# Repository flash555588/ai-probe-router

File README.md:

# ai-probe-router

AI-assisted KiCad probe/test interface designer. Automatically generates testpoints, maps probe pins to development board connectors, and validates placement against electrical, mechanical, and manufacturing constraints.

## Features

- **KiCad S-expression parser** — reads `.kicad_sch` and `.kicad_pcb` files, supports `gr_rect`, `gr_line`, `gr_circle` board outlines
- **Net classifier** — rule-based classification into power, ground, debug, communication, analog, high-speed, clock, reset, GPIO
- **Constraint-aware placement** — generates candidate positions scored by routing cost, board edge clearance, component collision avoidance, and probe spacing
- **Pin mapper** — maps target nets to development board pins using capability matching, current ratings, and user preferences
- **Schematic + PCB generation** — inserts testpoint symbols/footprints, connector symbols/footprints, protection circuits, fiducials, tooling holes, and keepout zones into KiCad files
- **Protection circuit generation** — series resistors for debug/reset signals (33/100 ohm), ferrite beads for power lines
- **Three probe layout modes** — distributed test pads, centralized pogo pad array, connector-based interface
- **Verification** — constraint validation, ERC/DRC via `kicad-cli`, coverage reports, manufacturing readiness reports
- **Human review gates** — flags high-speed, clock, analog, and high-current nets for mandatory review
- **Net class recommendations** — suggests trace width and clearance per net role
- **DSN export** — exports Specctra/Electra DSN for FreeRouting autorouter
- **Schema v2 module planning** - describes higher-level hardware modules such as SWD debug, GPIO expansion, and power monitoring, then selects a valid implementation from module libraries

## Installation

```bash
# Clone
git clone https://github.com/flash555588/ai-probe-router.git
cd ai-probe-router

# Core CLI + development checks (requires Python 3.12+)
uv pip install -e ".[dev]"

# Plugin shell GUI
uv pip install -e ".[plugin]"

# Optional CP-SAT solver support
uv pip install -e ".[solver]"

# Everything Python-side
uv pip install -e ".[all]"
```

### Capability Matrix

| Capability | Python extra | System dependency |
|------------|--------------|-------------------|
| Core CLI, reports, tests | `.[dev]` | none |
| Plugin shell GUI | `.[plugin]` | desktop display environment |
| 3D plugin preview | `.[plugin]` | `vtk` from the plugin extra |
| CP-SAT pin mapping | `.[solver]` | none |
| Native KiCad ERC/DRC/export | any | `kicad-cli` |
| FreeRouting bridge | any | Java + FreeRouting |

## Quick Start

### Inspect a PCB

```bash
apr inspect examples/minimal_project/main.kicad_pcb
```

### Generate testpoints

```bash
apr generate examples/sample_config.yaml -d examples/minimal_project
```

### Generate with dev board pin mapping

```bash
apr generate examples/full_config.yaml -d examples/minimal_project
```

### Validate existing testpoints

```bash
apr validate path/to/board.kicad_pcb
```

### Launch plugin shell (3D preview)

Requires `uv pip install -e ".[plugin]"`.

```bash
apr plugin-shell output/
apr plugin-shell output/ --step 3D_PCB1.step
```

## Configuration
Define your probe requirements in a YAML file:

```yaml
project:
  eda_tool: kicad
  board_file: main.kicad_pcb
  schematic_file: main.kicad_sch

probe_interface:
  type: test_pad          # test_pad | pogo_pad_array | connector
  side: top
  pad_diameter_mm: 1.5
  min_probe_spacing_mm: 2.54
  preferred_grid_mm: 2.54
  require_silkscreen_labels: true
  require_fiducials: true
  require_tooling_holes: true

nets_to_expose:
  - net: SWDIO
    role: debug
    required: true
    preferred_devboard_pins: [PA13]
  - net: GND
    role: ground
    required: true
    duplicate_probe_count: 4
  - net: 3V3
    role: power
    required: true
    current_ma: 300

routing_rules:
  default_trace_width_mm: 0.15
  power_trace_width_mm: 0.5

placement_rules:
  min_distance_from_board_edge_mm: 2.0

development_board:
  pin_database: path/to/dev_board_pins.yaml

protection:
  enabled: true
  debug:
    type: series_resistor
    value: "33"
    package: "0402"
  reset:
    type: series_resistor
    value: "100"
    package: "0402"
  power:
    type: ferrite_bead
    value: "600R@100MHz"
    package: "0603"
    ref_prefix: FB
```

### Schema v2 Functional Modules

Schema v2 keeps the old `nets_to_expose` format compatible, and also adds
module-level design intent:

```yaml
schema_version: 2

project:
  eda_tool: kicad
  board_file: main.kicad_pcb
  schematic_file: main.kicad_sch

hardware_platform:
  target_voltage_domains:
    - name: VDD_3V3
      voltage: 3.3
      max_current_ma: 800

functional_modules:
  - name: scalable_gpio
    type: gpio_expansion
    channels: 16
    depends_on: [debug_access]
    budget_area_mm2: 250
    preferred_region: top
    ai_hints:
      - type: sensitive_route
    allowed_interfaces: [i2c, spi]
    require_level_shift: true
    require_esd: true

routing_strategy:
  coarse_grid_mm: 5
  congestion_weight: 10
  sensitive_net_spacing_mm: 5

process_controls:
  strict_signoff: false
  require_autorouter_feedback: false
  scalability_module_warning_threshold: 20
  scalability_net_warning_threshold: 200
  waivers:
    - id: WV-1
      source: electrical_signoff
      issue_id: electrical_review_required
      owner: layout-review
      reason: external checklist completed
```

The module-planning pass is rule based. It writes selected implementations,
module library preflight diagnostics, module graph diagnostics, bus/power
reports, a per-module BOM, and routing feasibility corridors. It also reports
module, implementation, chip, and footprint version metadata for compatibility
and substitution review. Generated hierarchical sheet stubs are written under
`output/generated_modules/` when a schematic is available. AI hints are advisory
only and are reported when ignored. The process-control pass covers electrical
signoff gaps, power-integrity assumptions, DFM, fixture realism, library
governance, waivers, incremental diffs, scalability thresholds, autorouter
feedback, and reproducibility manifests.

## Architecture

```
ai_probe_router/
├── ai/                  # Net classifier
├── eda_adapters/kicad/  # S-expression parser, PCB/schematic read/write
├── models/              # Board, Net, Probe, Constraints, DevBoard, Protection
├── solvers/             # Constraint checker, placement solver, pin mapper, routing cost
├── routing/             # DSN export for autorouter
└── verification/        # Coverage, pin mapping, manufacturing readiness reports
```

**Design principle**: AI assists with classification and suggestions; deterministic rules enforce correctness. The constraint engine validates every placement — the system never trusts AI-generated geometry without verification.

## CLI Commands

| Command | Description |
|---------|-------------|
| `apr generate <config> [-d dir]` | Full pipeline: parse, place, generate, verify |
| `apr inspect <pcb_file>` | List nets with roles and pad counts |
| `apr inspect-sch <sch_file>` | List components, labels, wires |
| `apr validate <pcb_file>` | Validate existing testpoint placement |

## Output Files

After running `apr generate`, the `output/` directory contains:

Text reports, `bom_report.csv`, and generated module sheets include a deterministic
`APR-*` run ID so outputs from the same planning run can be traced together.

| File | Description |
|------|-------------|
| `*.kicad_pcb` | Updated PCB with testpoints, connector, fiducials, tooling holes, keepouts |
| `*.kicad_sch` | Updated schematic with testpoint symbols, connector, protection circuits |
| `*.kicad_pro` | KiCad project file carrying the configured design rules so native DRC validates against them |
| `testpoint_report.txt` | Coverage report with net class recommendations and review gates |
| `pin_mapping_report.txt` | Development board pin assignment table |
| `module_report.txt` | Schema v2 module selections, rejected alternatives, and review gates |
| `module_library_preflight_report.txt` | Module library YAML structure, metadata, duplicate, and request coverage checks |
| `module_graph_report.txt` | Module instances, dependencies, generated resources, graph diagnostics |
| `module_compatibility_report.txt` | Module, implementation, chip, footprint, and alternate compatibility matrix |
| `resource_allocation_report.json` | Deterministic bus and power allocation data for schema-v2 modules |
| `resource_optimization_report.json` | Advisory bus/rail optimization recommendations with no automatic mutation |
| `bus_report.txt` | Module bus grouping, I2C address conflicts, pull-up coverage |
| `power_report.txt` | Module voltage-domain and rail usage |
| `routing_feasibility_report.txt` | Coarse module corridor, congestion, and sensitivity analysis |
| `module_placement_report.txt` | Module regions, component placement scaffolds, probe/connector zones |
| `module_instantiation_report.txt` | Generated module sheet stubs and child schematic files |
| `generated_modules/*.kicad_sch` | Generated hierarchical module child sheets |
| `bom_report.csv` | Per-module generated component rows |
| `manufacturing_report.txt` | Manufacturing readiness summary |
| `design_process_report.txt` | Process gaps, waivers, signoff coverage, and next actions |
| `readiness_report.txt` | Top-level PASS, PASS_WITH_REVIEW, or BLOCKED verdict |
| `decision_manifest.json` | Run ID, tool versions, decisions, waivers, artifact hashes, and diff summary |
| `routing.dsn` | Specctra DSN for FreeRouting autorouter |

## Development

```bash
# Run tests
pytest --tb=short -ra -q

# Lint
ruff check .

# Audit Python dependencies
pip-audit --progress-spinner off
```

## License

MIT

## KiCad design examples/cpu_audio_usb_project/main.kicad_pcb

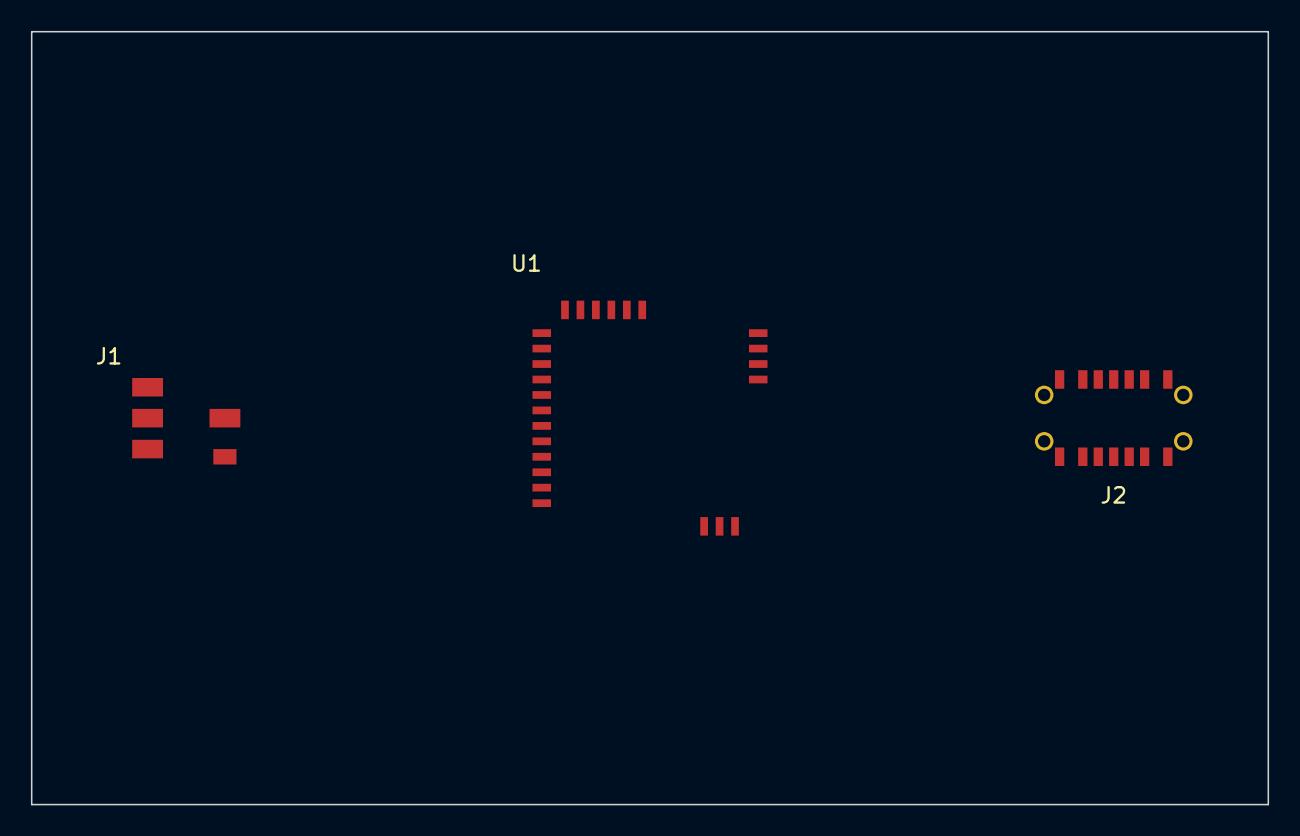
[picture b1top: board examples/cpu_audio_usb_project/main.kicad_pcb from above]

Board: 2 copper layers, 80.0 x 50.0 mm, 3 parts (0 on the bottom side), 10 nets, no tracks yet.

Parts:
J1: Headphone; Jack_3.5mm_CUI_SJ-3523-SMT
J2: USB-C; USB_C_Receptacle_HRO_TYPE-C-31-M-12
U1: STM32F405; LQFP-64

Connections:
3V3: U1.3, U1.14, U1.35, U1.49
GND: J2.A5, J2.B5, U1.4, U1.13, U1.15, U1.34, U1.48, U1.50
HP_DETECT: J1.5, U1.8
HP_L: J1.4, U1.5
HP_MIC: J1.1, U1.7
HP_R: J1.3, U1.6
USB_DM: J2.A7, J2.B7, U1.33
USB_DP: J2.A6, J2.B6, U1.32
USB_GND: J2.A1, J2.A12, J2.B1, J2.B12, J2.S1, J2.S2, J2.S3, J2.S4, U1.18
USB_VBUS: J2.A4, J2.A9, J2.B4, J2.B9, U1.16

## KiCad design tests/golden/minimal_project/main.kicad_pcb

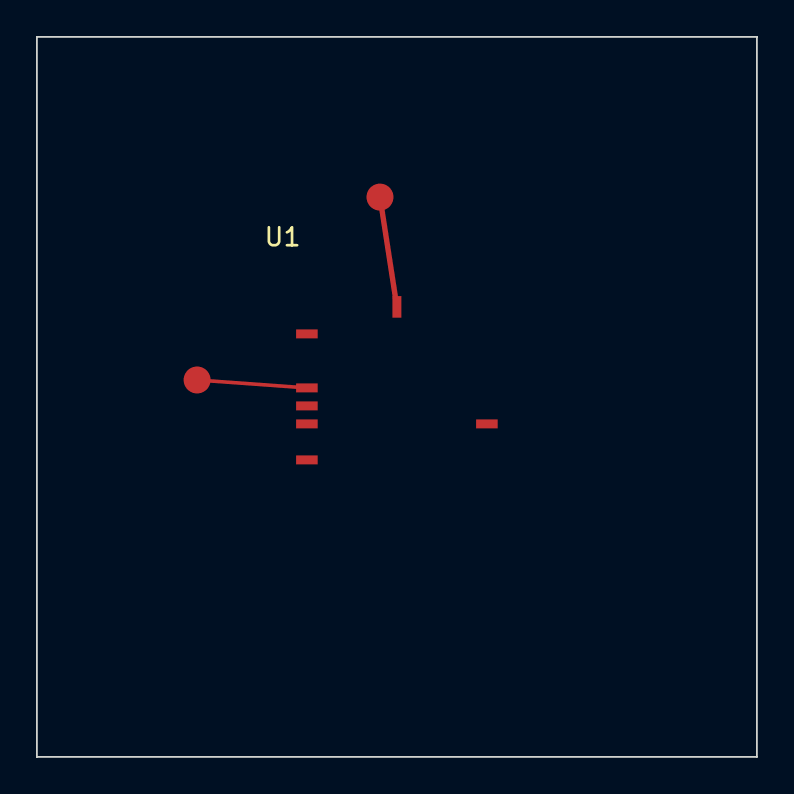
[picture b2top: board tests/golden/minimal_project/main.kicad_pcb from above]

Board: 2 copper layers, 40.0 x 40.0 mm, 3 parts (0 on the bottom side), 2 nets.

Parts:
TP1: TP_GND; TestPoint_Pad_D1.5mm
TP2: TP_SWDIO; TestPoint_Pad_D1.5mm
U1: STM32; LQFP-48

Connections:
GND: TP1.1, U1.24
SWDIO: TP2.1, U1.7

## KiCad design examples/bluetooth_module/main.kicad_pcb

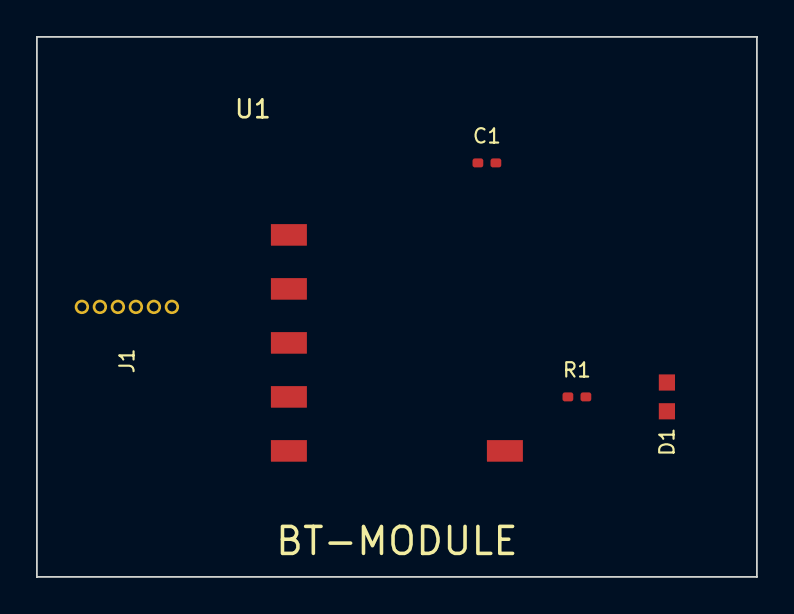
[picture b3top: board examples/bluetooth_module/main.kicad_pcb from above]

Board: 2 copper layers, 40.0 x 30.0 mm, 5 parts (0 on the bottom side), 7 nets, no tracks yet.

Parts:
C1: 100n; C_0402_1005Metric
D1: STATUS_LED; LED_0603_1608Metric
J1: CONN; PinHeader_1x06_P1.00mm_Vertical
R1: 1k; R_0402_1005Metric
U1: HC-05; Bluetooth_HC-05

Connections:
EN: J1.6, U1.6
GND: C1.2, D1.1, J1.2, U1.2
LED: D1.2, R1.2
STATE: J1.5, U1.5
UART_RX: J1.4, U1.4
UART_TX: J1.3, U1.3
VCC: C1.1, J1.1, R1.1, U1.1

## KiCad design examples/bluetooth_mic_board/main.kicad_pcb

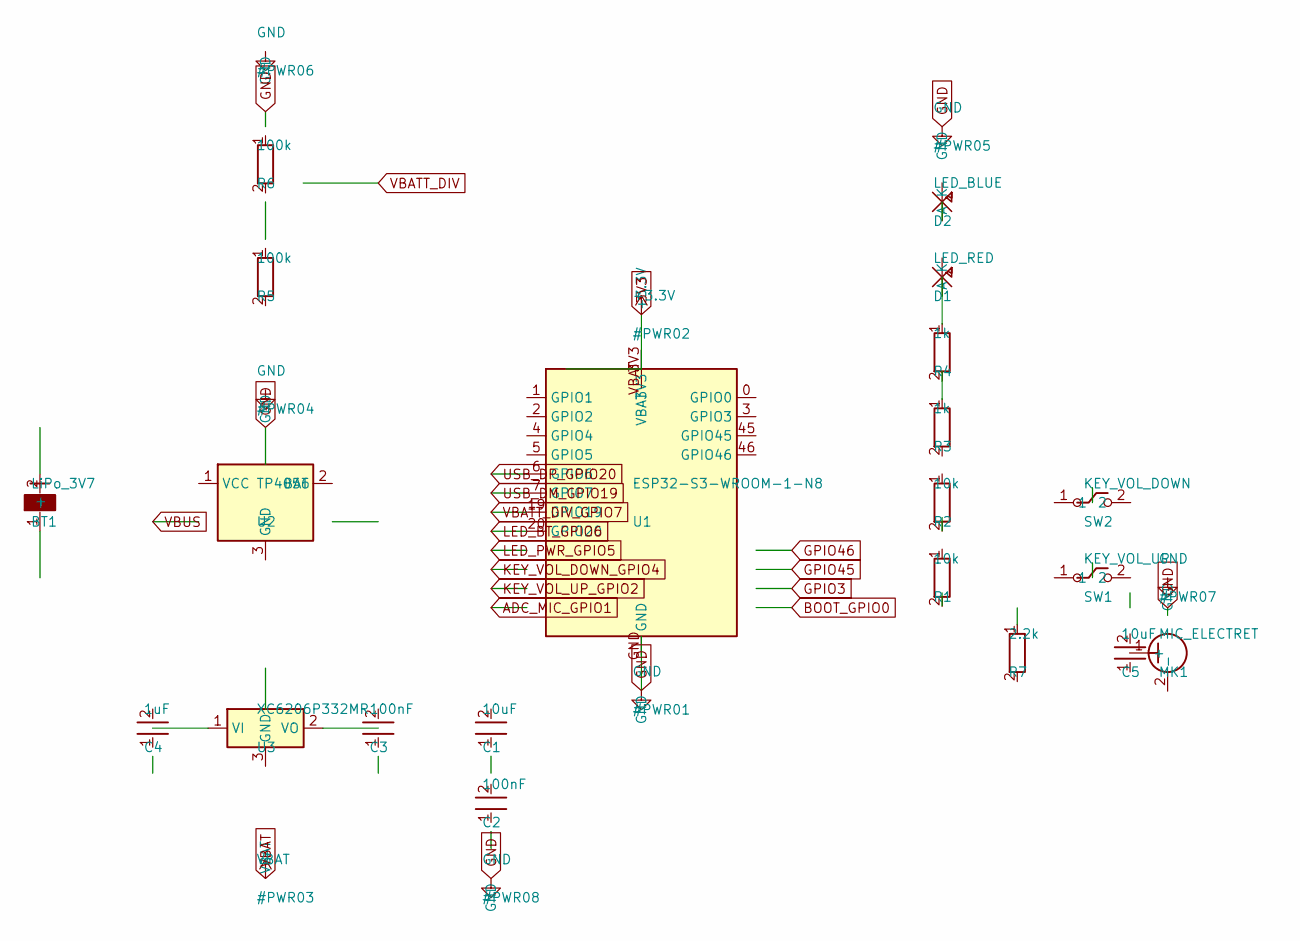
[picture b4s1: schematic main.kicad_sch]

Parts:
BT1: LiPo_3V7
C1, C5: 10uF
C2, C3: 100nF
C4: 1uF
D1: LED_RED
D2: LED_BLUE
MK1: MIC_ELECTRET
R1, R2: 10k
R3, R4: 1k
R5, R6: 100k
R7: 2.2k
SW1: KEY_VOL_UP
SW2: KEY_VOL_DOWN
U1: ESP32-S3-WROOM-1-N8
U2: TP4056
U3: XC6206P332MR

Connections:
3V3: U1.3V3, U3.2 (VO)
ADC_MIC_GPIO1: MK1.1 (+), U1.1 (GPIO1)
BOOT_GPIO0: U1.0 (GPIO0)
GND: BT1.2 (-), D1.1 (K), D2.1 (K), MK1.2 (-), SW1.2, SW2.2, U1.GND, U2.3 (GND), U3.3 (GND); also elsewhere on the board
GPIO3: U1.3 (GPIO3)
GPIO45: U1.45 (GPIO45)
GPIO46: U1.46 (GPIO46)
KEY_VOL_DOWN_GPIO4: SW2.1, U1.4 (GPIO4)
KEY_VOL_UP_GPIO2: SW1.1, U1.2 (GPIO2)
LED_BT_GPIO6: D2.2 (A), U1.6 (GPIO6)
LED_PWR_GPIO5: D1.2 (A), U1.5 (GPIO5)
USB_DM_GPIO19: U1.19 (GPIO19); also elsewhere on the board
USB_DP_GPIO20: U1.20 (GPIO20); also elsewhere on the board
VBAT: BT1.1 (+), U1.VBAT, U2.2 (BAT), U3.1 (VI)
VBATT_DIV_GPIO7: U1.7 (GPIO7)
VBUS: U2.1 (VCC); also elsewhere on the board

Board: 2 copper layers, 22 parts (0 on the bottom side), 11 nets, no tracks yet.

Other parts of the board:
J1: USB_TYPE-C; USB_C_Receptacle_HRO_TYPE-C-31-M-12

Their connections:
GND: J1.A1, J1.A12; also elsewhere on the board
USB_DM_GPIO19: J1.A5; also elsewhere on the board
USB_DP_GPIO20: J1.A6; also elsewhere on the board
VBUS: J1.A4, J1.A9; also elsewhere on the board

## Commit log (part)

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2026-06-06 feat: ai-probe-router v1.0.0
    AI-assisted KiCad probe/test interface designer.
    Core features:
    - KiCad schematic/PCB s-expression parser with gr_rect/gr_circle support
    - Rule-based net classifier (power, ground, debug, communication, etc.)
    - Constraint-aware probe placement solver with routing cost estimation
    - Greedy pin mapper for development board connector assignment
2026-06-06 feat: protection circuits + README + CI + full config
    - Add protection circuit generation (series resistors for debug/reset,
    ferrite beads for power) between MCU nets and probe testpoints
    - Add ai_probe_router/models/protection.py: ProtectionComponent,
    ProtectionRules, ProtectionType, ROLE_PROTECTION_DEFAULTS
    - Extend sch_writer with resistor/ferrite lib symbols and
    add_protected_testpoint_symbol()
2026-06-06 feat: fiducials and tooling holes + probe pad silkscreen labels
    - Add add_fiducial_footprint() and add_tooling_hole_footprint() to pcb_writer
    - Engine auto-places fiducials at 3 board corners and tooling holes
    along bottom edge when config requires them
    - Enable fiducials/tooling_holes in examples/full_config.yaml
    - Add tests/test_fiducial_tooling.py (6 tests)
    101 tests passing, ruff clean.
2026-06-06 feat: keepout zone generation for probe pads and connector
    - Add add_keepout_zone() to pcb_writer: rectangular keepout with
    tracks/vias/pads/copperpour/footprints all not_allowed
    - Engine adds keepout around every placed testpoint (pad + 1mm margin)
    - Engine adds keepout around development-board connector
    - Add tests/test_keepout.py (3 tests)
    107 tests passing, ruff clean.
2026-06-06 feat: net class recommendations (trace width / clearance)
    - Add NetCoverage.trace_width_mm and clearance_mm fields
    - Engine assigns net class values based on role and current:
    - power >500mA: 0.5mm trace, 0.2mm clearance
    - power/ground: 0.3mm trace, 0.15mm clearance
    - high_speed/clock: 0.15mm trace, 0.2mm clearance
    - analog: 0.2mm trace, 0.25mm clearance
2026-06-06 feat: DSN (Specctra) export for autorouting
    - Add ai_probe_router/routing/dsn_export.py with export_dsn()
    - Exports board outline, netlist, placement, library outlines,
    and basic design rules (width/clearance)
    - Engine auto-generates routing.dsn in output directory on every run
    - Add tests/test_dsn_export.py (5 tests)
    118 tests passing, ruff clean.
2026-06-06 feat: differential pair support in pin mapper
    - Add ProbeRequirement.pair_net_name for differential pair pairing
    - Pin mapper detects differential pairs and assigns them to adjacent pins
    - Add _build_pair_map(), _is_adjacent(), _assign_differential_pair()
    - Add high_speed capability mapping for USB/ETH nets
    - Config parses pair_with from YAML
    - Add tests for differential pair mapping and fallback
2026-06-06 feat: SES (Specctra Session) import for routed tracks/vias
    - Add ai_probe_router/routing/ses_import.py with import_ses()
    - Parses wire paths and vias from FreeRouting SES output
    - Converts to KiCad PCB segment/via nodes with proper layer mapping
    - Completes DSN->FreeRouting->SES->KiCad routing loop
    - Add tests/test_ses_import.py (3 tests)
    123 tests passing, ruff clean.
2026-06-06 feat: complete CLI tests, fix lint errors, and clean up design
    - Add comprehensive CLI tests (9 tests) covering inspect, inspect-sch,
    validate, generate, route commands; CLI coverage: 0% -> 85%
    - Fix 6 ruff lint errors in tests (unused vars, long lines, unused imports)
    - Remove redundant >= 0 checks in _place_fiducials_and_tooling (engine.py)
    - Simplify _net_role by removing unused board parameter (drc_repair_agent.py)
    - Fix PEP 8 blank line before _run in cli_runner.py
2026-06-07 feat(advanced-iot): 19-net advanced config, diff pairs, impedance, thermal
    - examples/iot_sensor_node_advanced_config.yaml: Schema v2 config with
    5 functional modules (debug, power, analog, RS-485, GPIO expansion)
    19 nets including I2C, SPI, CAN diff pair, USB diff pair, ADC
    impedance_control rules for USB (90Ω) and CAN (120Ω)
    thermal_analysis export config
    - examples/iot_sensor_node_project/: complete KiCad project with all
2026-06-07 fix(pin_mapper): restrict GPIO fallback to differential pairs
    - _role_to_capabilities now takes pair_net_name parameter
    - GPIO fallback for high_speed only enabled when part of a diff pair
    - Fixes regression where single high_speed nets mapped to any GPIO
    - Updates test_differential_pair_fallback_when_no_adjacent to use
    a 1-pin board (impossible to place pair)
    302 tests passed
2026-06-07 build: add streamlit/matplotlib UI deps and 'all' extra
    - Add [project.optional-dependencies] ui = [streamlit, matplotlib]
    - Add 'all' extra that pulls in web + ui + solver
    302 tests pass
2026-06-08 feat: diff pair trace length skew report
    - Add trace_length_mm field to NetCoverage
    - Add _trace_length() helper in engine.py to compute route length
    - Create DiffPairSkewReport with per-pair length comparison
    - Generate diff_pair_skew_report.txt in output directory
    - Threshold: ±0.5mm or ±5% skew
    302 tests pass
2026-06-08 feat(ui): thermal heatmap + diff pair skew in Streamlit
    - Add _render_thermal_heatmap() using matplotlib scatter + hot colormap
    - Split PCB preview into Layout / Thermal tabs
    - Add diff pair skew report expander
    302 tests pass
2026-06-08 style: fix ruff lint across repository
    - Add ruff exclude for render scripts, examples, and scripts
    - Fix E501 line-too-long in core source and tests
    - Fix F841 unused-variable in tests
    - Apply ruff --fix for import sorting and unused imports
    Fixes CI lint failures on PR #1
2026-06-08 feat(verification): design-process report, readiness report, and process controls (#1)
    * feat(verification): design-process report, readiness report, and process controls
    - Add DesignProcessReport with coverage, waiver, and gap analysis
    - Add ReadinessReport as top-level signoff verdict across reports
    - Add ProcessControls / ProcessWaiver models for traceability
    - Add ModuleLibraryPreflight and ModuleLibraryPreflightReport
    - Add DecisionManifest for incremental diff tracking
2026-06-08 Add readiness safety baseline
2026-06-08 Add pin mapper mode configuration
2026-06-08 Add pin mapper compare mode
2026-06-08 Report CP-SAT pin mapping readiness issues
2026-06-08 Add JSON schemas for chip, module, dev-board, and project config
2026-06-08 Add CLI command and tests
2026-06-08 Add resource allocator config and core solvers
2026-06-08 Add resource allocator tests and docs
2026-06-08 Add deterministic footprint preview planner
2026-06-08 Add module footprint preview tests and docs
2026-06-08 Add report loader and VTK 3D view for plugin shell
2026-06-08 Add plugin shell tests, docs, and dependencies
2026-06-08 Add PR7.1 3D plugin shell: STEP loader, footprint overlays, severity filters, detail panel
2026-06-08 PR5 production-grade enhancements: config, priority, thresholds, simulation
    - Add and to
    - Parse new RA config fields from YAML (,
    )
    - Add field to with YAML parsing
    - Bus allocator: sort modules by priority descending before allocation
    - Power domain solver: accept and kwargs,
2026-06-08 Add generated KiCad PCB constraints for Audio Player
    - main.kicad_pcb: full 6-layer PCB skeleton with board outline,
    14 net classes, and digital/analog keepout zones
    - netclasses.kicad_pcb: standalone net class definitions for import
    - zones.kicad_pcb: standalone keepout zone definitions for import
    Generated by generate_constraints.py from audio_player_config.yaml.
2026-06-08 Fix PCB format for KiCad 8.0 compatibility
    - Replace gr_line board edge with gr_rect (KiCad 8.0 format)
    - Replace zone tstamp with uuid (KiCad 8.0 requirement)
    - Add uuid to all zones and board edge rectangle
    - Clean ;; comments from netclasses.kicad_pcb and zones.kicad_pcb
    - Add uuid import to generate_constraints.py
    Note: Only main.kicad_pcb is a complete PCB file.
2026-06-08 Fix schematic: remove KiCad-incompatible ;; comments, 54 lines removed, 551 lines remaining, balanced parens verified
2026-06-08 Harden KiCad schematic export
2026-06-09 Add CircuitSpec preflight ERC
2026-06-09 Harden delivery contract
2026-06-09 Add config schema validation layer
2026-06-09 Harden CI supply chain checks
2026-06-09 Upload native KiCad CI reports
2026-06-09 Add paired probe placement awareness
2026-06-09 Gate required autorouter feedback failures
2026-06-09 Gate strict native KiCad validation
2026-06-09 Validate generated outputs in native CI
2026-06-09 Extract autorouter pipeline contract
2026-06-09 Extract module planning pipeline stage
2026-06-09 Use delivery artifact stage for blocked module runs
2026-06-09 Cover audio player module library types
2026-06-09 Validate plugin signoff evidence
2026-06-09 Run native KiCad gate on pull requests
2026-06-09 fix: harden kicad-cli subprocess decoding on non-UTF-8 locales
    native_validation_runner ran kicad-cli via subprocess.run(text=True)
    without an explicit encoding. On non-UTF-8 locales (e.g. Windows cp936)
    the reader thread fails to decode kicad-cli output, leaving
    completed.stdout=None, which then crashed _write_text(). This cascaded
    into 24 test failures on machines that actually have KiCad installed,
    while CI stayed green because it lacks kicad-cli and took the
2026-06-09 fix: only block native signoff on error-severity DRC/ERC findings
    The native validation gate treated every DRC/ERC finding as blocking,
    regardless of severity. KiCad reports library-link issues
    (lib_footprint_mismatch / lib_footprint_issues) as warnings, including
    for the testpoint footprints this tool generates. Under strict_signoff
    or require_manufacturing_exports those benign warnings hard-failed
    apr generate, which kept the native-kicad CI gate red on the example
2026-06-10 fix: make standalone strict native validator severity-aware
    The native-kicad CI gate runs scripts/kicad_native_validate.py --strict,
    which goes through native_validation_runner's own status/return-code
    logic (separate from the engine's apply_native_validation path). That
    logic still failed on any finding and on any non-zero kicad-cli exit:
    - _status / _return_code treated every finding as blocking and any
    non-zero command exit as a failure. kicad-cli's --exit-code-violations
2026-06-10 refactor: centralize external tool subprocess decoding
2026-06-10 Add native KiCad baseline governance gate
2026-06-10 feat: full connector allocation + library migration + engine wiring
    - Implement connector_allocator with minimize_spread / group_by_function / none
    - Add connector readiness codes (CONFLICT, RESERVED_OVERRIDE, NEAR_LIMIT)
    - Wire connector allocation into engine.py (_run_phase2 returns tuple,
    _attach_connector_allocation called when resource_allocator.enable)
    - Move libraries/ into ai_probe_router/libraries/ for wheel packaging
    - Archive stray root files (render scripts, PNGs) to scripts/ and docs/images/
2026-06-11 feat(verification): add metric-based quality gate
    - quality_gate.py: replaces file-existence checks with threshold assertions
    on coverage %, unrouted connections, ERC/DRC violations, and route bends
    - ci/thresholds/minimal.json: hardened thresholds requiring 100% coverage,
    zero unrouted connections, and ERC/DRC pass
    - CLI --quality-gate flag wires thresholds into the generate command
    - Unit tests for all gate pass/fail conditions
2026-06-11 refactor(engine): split monolithic engine into staged pipeline
    Replace the 904-line single-file engine.py with a thin orchestrator over
    14 individually-testable pipeline stages:
    - engine_pipeline.py: PipelineContext + stage definitions
    - phase1_probes.py: probe placement, protection, escape routing
    - phase2_pinmap.py: development-board pin mapping + connector synthesis
    - run_id.py: deterministic run-id fingerprinting
2026-06-11 docs(ci): harden CI quality gates and update README
    - CI native-kicad job now runs with --quality-gate ci/thresholds/minimal.json
    so the gate enforces 100% coverage, zero unrouted connections, and ERC/DRC
    pass (replacing file-existence-only checks)
    - README artifact table gains .kicad_pro entry explaining design-rule
    carry-through to native DRC validation
